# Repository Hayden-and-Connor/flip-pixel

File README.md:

# flip-pixel
strictly worse than regular pixels

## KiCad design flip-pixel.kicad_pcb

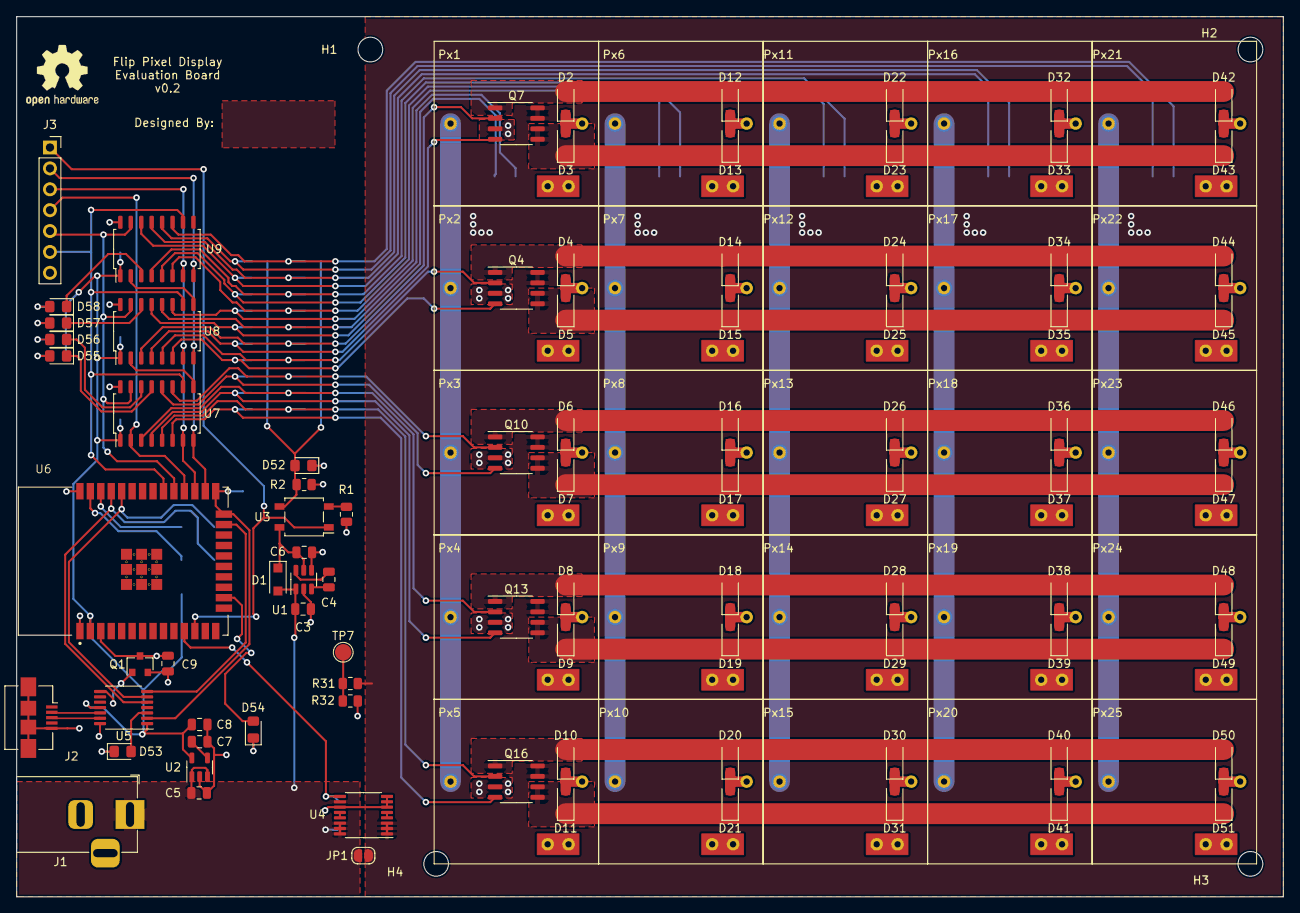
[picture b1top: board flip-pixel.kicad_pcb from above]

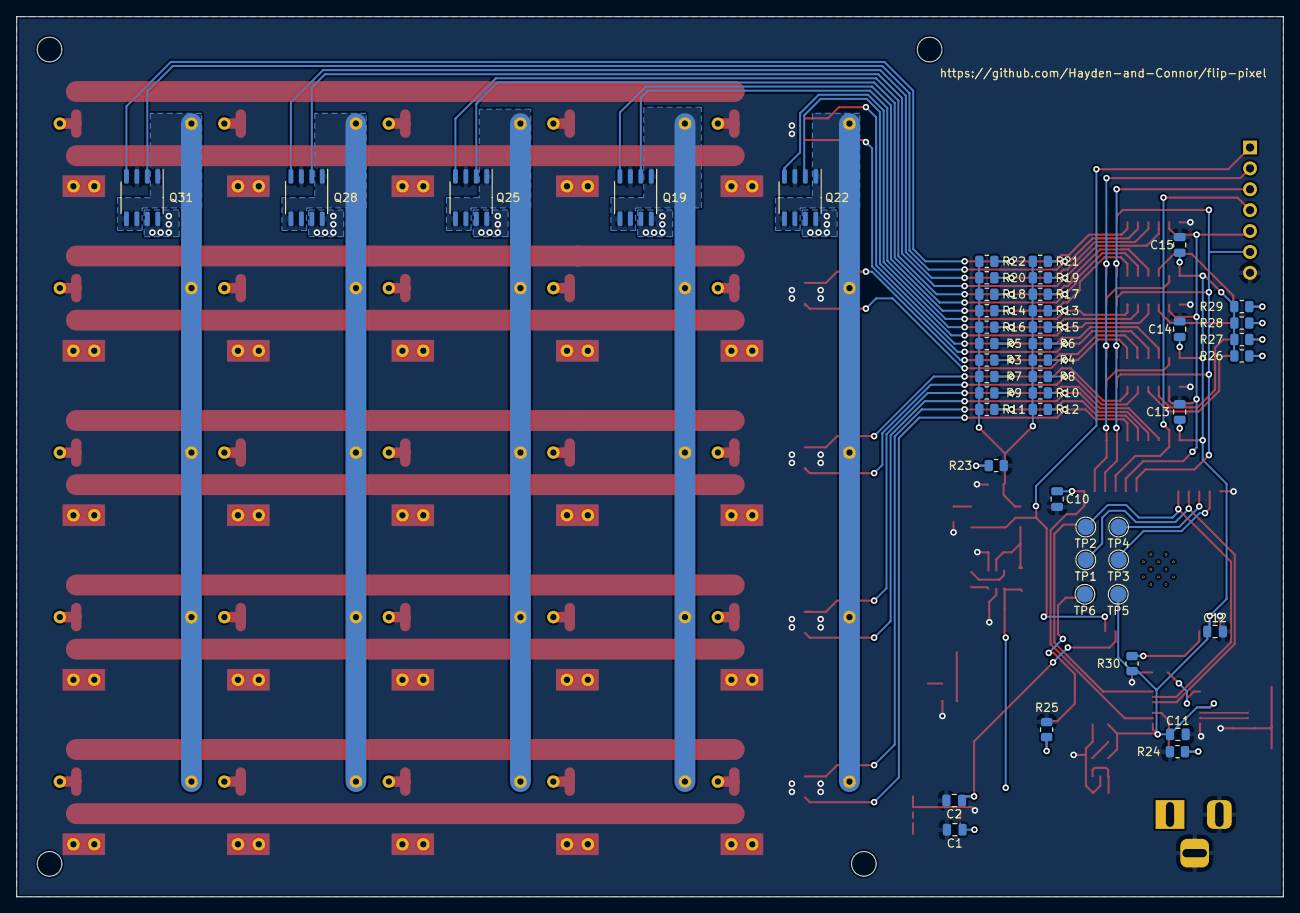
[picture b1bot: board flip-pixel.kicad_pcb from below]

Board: 2 copper layers, 154.0 x 107.0 mm, 166 parts (47 on the bottom side), 105 nets.

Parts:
C1, C9, C11, C12, C13, C14, C15: 0.1uF; C_0805_2012Metric
C2, C3, C4, C5, C6, C7, C8: C; C_0805_2012Metric
C10: 1uF; C_0805_2012Metric
D1, D2, D3, D4, D5, D6, D7, D8, D9, D10, D11, D12, D13, D14, D15, D16, D17, D18, D19, D20, D21, D22, D23, D24, D25, D26, D27, D28, D29, D30, D31, D32, D33, D34, D35, D36, D37, D38, D39, D40, D41, D42, D43, D44, D45, D46, D47, D48, D49, D50, D51: Diode; D_SOD-123F
D52, D53, D54, D55, D56, D57, D58: LED_Green; LED_0805_2012Metric_Pad1.15x1.40mm_HandSolder
H1, H2, H3, H4: MountingHole; MountingHole_3mm
J1: Barrel-Jack; BarrelJack_Horizontal
J2: MicroUSB; USB_Micro-B_Amphenol_10104110_Horizontal
J3: Conn_01x07_Female; PinSocket_1x07_P2.54mm_Vertical
JP1: BypassJumper; SolderJumper-2_P1.3mm_Open_RoundedPad1.0x1.5mm
LOGO1: Logo_Open_Hardware_Small; OSHW-Logo2_9.8x8mm_SilkScreen
Px1, Px2, Px3, Px4, Px5, Px6, Px7, Px8, Px9, Px10, Px11, Px12, Px13, Px14, Px15, Px16, Px17, Px18, Px19, Px20, Px21, Px22, Px23, Px24, Px25: FlipPixel; Flip-Pixel
Q1: DMN62D0U-7; SOT-23
Q4, Q7, Q10, Q13, Q16, Q19, Q22, Q25, Q28, Q31: STS8DN6LF6AG; SO-8_3.9x4.9mm_P1.27mm
R1, R2, R3, R4, R5, R6, R7, R8, R9, R10, R11, R12, R13, R14, R15, R16, R17, R18, R19, R20, R21, R22, R23, R24, R25, R26, R27, R28, R29, R31, R32: R; R_0805_2012Metric
R30: 10k; R_0805_2012Metric
TP1, TP2, TP3, TP4, TP5, TP6, TP7: TestPoint; TestPoint_Pad_D2.0mm
U1: LM2665M6; SOT-23-6
U2: TPS79933; SOT-23-5
U3: ASSR-4118-503E; SO-4_4.4x4.3mm_P2.54mm
U4: INA250A3; TSSOP-16_4.4x5mm_P0.65mm
U5: MCP2221A; TSSOP-14_4.4x5mm_P0.65mm
U6: ESP32; MODULE_ESP32-WROOM-32
U7, U8, U9: NPIC6C596ADJ; SOIC-16_4.55x10.3mm_P1.27mm

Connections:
+3V3: C8.1, C11.1, C12.1, C13.1, C14.1, C15.1, R26.1, R27.1, R28.1, R29.1, R30.1, TP5.1, U2.5 (OUT), U5.1 (Vdd), U5.11 (Vusb), U6.2 (3v3), U7.1 (Vcc), U8.1 (Vcc), U9.1 (Vcc)
+5V: C1.1, C3.1, C5.1, D1.2 (A), J1.1, JP1.1 (A), U1.1 (V+), U2.1 (IN), U2.3 (EN), U4.10 (VS), U4.14 (IN+), U4.15 (IN+), U4.16 (IN+)
/Col_3: Px11.2, Px12.2, Px13.2, Px14.2, Px15.2, Q25.1, Q25.5, Q25.6
/Controller/IND_SR1_1: D55.1, U7.13 (Q6)
/Controller/IND_SR1_2: D56.1, U7.14 (Q7)
/Controller/IND_SR2: D57.1, U8.14 (Q7)
/Controller/IND_SR3: D58.1, U9.3 (Q0)
/Controller/SCL: TP4.1, U6.36 (IO22)
/Controller/SDA: TP3.1, U6.37 (IO23)
/Controller/bootmode_select: C10.1, U5.2 (GP0), U6.24 (IO2), U6.25 (IO0)
/Controller/data: J3.4, U6.28 (IO17), U7.2 (DS)
/Controller/esp_reset: Q1.1 (G), U5.8 (GP3)
/Controller/esp_rx: TP2.1, U5.6 (UTx), U6.34 (RXD0)
/Controller/esp_tx: TP1.1, U5.5 (URx), U6.35 (TXD0)
/Controller/mcu_indicator: D54.2, U6.16 (IO13)
/Controller/shift_clock: J3.5, U6.29 (IO5), U7.15 (SHCP), U8.15 (SHCP), U9.15 (SHCP)
/Controller/storage_clock: J3.6, U6.30 (IO18), U7.10 (STCP), U8.10 (STCP), U9.10 (STCP)
/Controller/usb_indicator: D53.2, U5.3 (GP1)
/Controller/~esp_reset: C9.1, Q1.3 (D), R30.2, U6.3 (EN)
/Controller/~master_reset: J3.3, U6.27 (IO16), U7.7 (~MR), U8.7 (~MR), U9.7 (~MR)
/Controller/~output_enable: J3.2, U6.26 (IO4), U7.8 (~OE), U8.8 (~OE), U9.8 (~OE)
/Controller/~silent_boot: U5.7 (GP2), U6.23 (IO15)
/GateDrive: D52.2, R2.1, R3.1, R4.1, R5.1, R6.1, R7.1, R8.1, R9.1, R10.1, R11.1, R12.1, R13.1, R14.1, R15.1, R16.1, R17.1, R18.1, R19.1, R20.1, R21.1, R22.1, U3.3
/High: D2.2 (A), D12.2 (A), D22.2 (A), D32.2 (A), D42.2 (A), Q7.1
/High_1: D6.2 (A), D16.2 (A), D26.2 (A), D36.2 (A), D46.2 (A), Q10.1
/High_2: Px21.2, Px22.2, Px23.2, Px24.2, Px25.2, Q31.1, Q31.5, Q31.6
/High_3: Px16.2, Px17.2, Px18.2, Px19.2, Px20.2, Q28.1, Q28.5, Q28.6
/High_4: Px6.2, Px7.2, Px8.2, Px9.2, Px10.2, Q19.1, Q19.5, Q19.6
/Low: D5.1 (K), D15.1 (K), D25.1 (K), D35.1 (K), D45.1 (K), Q4.5, Q4.6
/Low_1: Px1.2, Px2.2, Px3.2, Px4.2, Px5.2, Q22.1, Q22.5, Q22.6
/Row_1_L: D3.1 (K), D13.1 (K), D23.1 (K), D33.1 (K), D43.1 (K), Q7.5, Q7.6
/Row_2_H: D4.2 (A), D14.2 (A), D24.2 (A), D34.2 (A), D44.2 (A), Q4.1
/Row_3_L: D7.1 (K), D17.1 (K), D27.1 (K), D37.1 (K), D47.1 (K), Q10.5, Q10.6
/Row_4_H: D8.2 (A), D18.2 (A), D28.2 (A), D38.2 (A), D48.2 (A), Q13.1
/Row_4_L: D9.1 (K), D19.1 (K), D29.1 (K), D39.1 (K), D49.1 (K), Q13.5, Q13.6
/Row_5_H: D10.2 (A), D20.2 (A), D30.2 (A), D40.2 (A), D50.2 (A), Q16.1
/Row_5_L: D11.1 (K), D21.1 (K), D31.1 (K), D41.1 (K), D51.1 (K), Q16.5, Q16.6
/matrix_current: C2.1, U4.9 (OUT), U6.11 (IO26)
/matrix_enable: J3.1, U3.1, U6.12 (IO27)
/usb_D+: J2.3 (D+), U5.13 (D+)
/usb_D-: J2.2 (D-), U5.12 (D-)
GND: C1.2, C2.2, C3.2, C5.2, C6.2, C7.2, C8.2, C9.2, C10.2, C11.2, C12.2, C13.2, C14.2, C15.2, J1.2, J1.3, J2.5 (GND), J2.6 (Shield), J3.7, Q1.2 (S), Q4.3, Q7.3, Q10.3, Q13.3, Q16.3, Q19.3, Q22.3, Q25.3, Q28.3, Q31.3, R1.2, R2.2, R23.2, R24.2, R25.2, R32.2, TP6.1, U1.2 (GND), U1.4 (SD), U2.2 (GND), U4.6 (GND), U4.7 (REF), U4.8 (GND), U4.11 (GND), U5.14 (Vss), U6.1 (GND), U6.38 (GND), U7.16 (GND), U8.16 (GND), U9.16 (GND)
MatrixControl1: Q22.4, R16.2, U8.12 (Q5)
MatrixControl2: Q22.2, R15.2, U8.13 (Q6)
MatrixControl3: Q19.2, R13.2, U8.11 (Q4)
MatrixControl4: Q19.4, R14.2, U9.6 (Q3)
MatrixControl5: Q25.2, R17.2, U9.5 (Q2)
MatrixControl6: Q25.4, R18.2, U9.4 (Q1)
MatrixControl7: Q28.2, R19.2, U9.14 (Q7)
MatrixControl8: Q28.4, R20.2, U9.13 (Q6)
MatrixControl9: Q31.2, R21.2, U9.12 (Q5)
MatrixControl10: Q31.4, R22.2, U9.11 (Q4)
MatrixControl11: Q7.2, R5.2, U8.3 (Q0)
MatrixControl12: Q7.4, R6.2, U8.4 (Q1)
MatrixControl13: Q4.2, R3.2, U8.5 (Q2)
MatrixControl14: Q4.4, R4.2, U8.6 (Q3)
MatrixControl15: Q10.2, R7.2, U7.11 (Q4)
MatrixControl16: Q10.4, R8.2, U7.12 (Q5)
MatrixControl17: Q13.2, R9.2, U7.3 (Q0)
MatrixControl18: Q13.4, R10.2, U7.4 (Q1)
MatrixControl19: Q16.2, R11.2, U7.5 (Q2)
MatrixControl20: Q16.4, R12.2, U7.6 (Q3)
MatrixPower: JP1.2 (B), Q4.7, Q4.8, Q7.7, Q7.8, Q10.7, Q10.8, Q13.7, Q13.8, Q16.7, Q16.8, Q19.7, Q19.8, Q22.7, Q22.8, Q25.7, Q25.8, Q28.7, Q28.8, Q31.7, Q31.8, R31.1, U4.1 (IN-), U4.2 (IN-), U4.3 (IN-)
unnamed: C4.1, U1.6 (CAP+)
unnamed: C4.2, U1.3 (CAP-)
unnamed: C6.1, D1.1 (K), U1.5 (OUT), U3.4
unnamed: C7.1, U2.4 (NR)
unnamed: D2.1 (K), D3.2 (A), Px1.1
unnamed: D4.1 (K), D5.2 (A), Px2.1
unnamed: D6.1 (K), D7.2 (A), Px3.1
unnamed: D8.1 (K), D9.2 (A), Px4.1
unnamed: D10.1 (K), D11.2 (A), Px5.1
unnamed: D12.1 (K), D13.2 (A), Px6.1
unnamed: D14.1 (K), D15.2 (A), Px7.1
unnamed: D16.1 (K), D17.2 (A), Px8.1
unnamed: D18.1 (K), D19.2 (A), Px9.1
unnamed: D20.1 (K), D21.2 (A), Px10.1
unnamed: D22.1 (K), D23.2 (A), Px11.1
unnamed: D24.1 (K), D25.2 (A), Px12.1
unnamed: D26.1 (K), D27.2 (A), Px13.1
unnamed: D28.1 (K), D29.2 (A), Px14.1
unnamed: D30.1 (K), D31.2 (A), Px15.1
unnamed: D32.1 (K), D33.2 (A), Px16.1
unnamed: D34.1 (K), D35.2 (A), Px17.1
unnamed: D36.1 (K), D37.2 (A), Px18.1
unnamed: D38.1 (K), D39.2 (A), Px19.1
unnamed: D40.1 (K), D41.2 (A), Px20.1
unnamed: D42.1 (K), D43.2 (A), Px21.1
unnamed: D44.1 (K), D45.2 (A), Px22.1
unnamed: D46.1 (K), D47.2 (A), Px23.1
unnamed: D48.1 (K), D49.2 (A), Px24.1
unnamed: D50.1 (K), D51.2 (A), Px25.1
unnamed: D52.1, R23.1
unnamed: D53.1, R24.1
unnamed: D54.1, R25.1
unnamed: D55.2, R26.2
unnamed: D56.2, R27.2
unnamed: D57.2, R28.2
unnamed: D58.2, R29.2
unnamed: R1.1, U3.2
unnamed: R31.2, R32.1, TP7.1
unnamed: U4.4 (SH-), U4.5 (VIN-)
unnamed: U4.12 (VIN+), U4.13 (SH+)
unnamed: U7.9 (Q7S), U8.2 (DS)
unnamed: U8.9 (Q7S), U9.2 (DS)

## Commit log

2020-06-15 Started work, drew schematic for 5x5 matrix and driving circuitry
2020-06-18 Added charge pump for gate driving, MicroController, and Power Connector
2020-06-21 Started work on layout
2020-06-21 Pixel Matrix and started Driving Circuits
2020-06-22 Layout for single driving circuit
2020-06-22 updated gitignore to ignore plugin log files
2020-06-22 Fixed a footprint mistake
2020-06-22 Replicated driving layout to all rows / columns
2020-06-22 Updated references for pixels
2020-06-23 adjustments for row drivers
2020-06-23 edge cuts
2020-06-23 Added 3D model to Power FET footprint
2020-06-23 Traces Routed for Charge Pump
2020-06-24 Added Current Sensor to Schematic
2020-06-25 starting trace routing
2020-06-26 Routed from drivers to controller
2020-06-26 Updated Pins to match routes
2020-06-26 All traces routed
2020-06-29 switched to new current sensor
2020-06-29 BOM config file
2020-06-29 stopped tracking cached library files
2020-06-29 Updated All Traces
2020-06-29 Logos and SilkScreen
2020-09-08 Began work on 0.2
2020-09-11 More work on 0.2 schematic
2020-09-11 changed files
2020-09-13 more layout work
2020-09-14 Ready for Manufacture
2020-12-02 small tweaks and version migration
